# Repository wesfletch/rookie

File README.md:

# rookie

A differential-drive robot. The SBC runs ROS; an RPi Pico handles motor control and low-level I/O.

## Dev environment

Requires Docker.

```bash
# First-time setup (installs git hooks)
./rookie setup

# Build the dev container
./rookie build

# Run the dev container
./rookie run
```

All subsequent build steps run inside the container. The `src/` directory is mounted at `~/workspace/`.

## Building

See the README in each subdirectory:

- [`src/pico_interface`](src/pico_interface/README.md) — shared interface/messaging library (build first)
- [`src/rookie_pico`](src/rookie_pico/README.md) — Pico firmware
- [`src/ros`](src/ros/README.md) — ROS workspace

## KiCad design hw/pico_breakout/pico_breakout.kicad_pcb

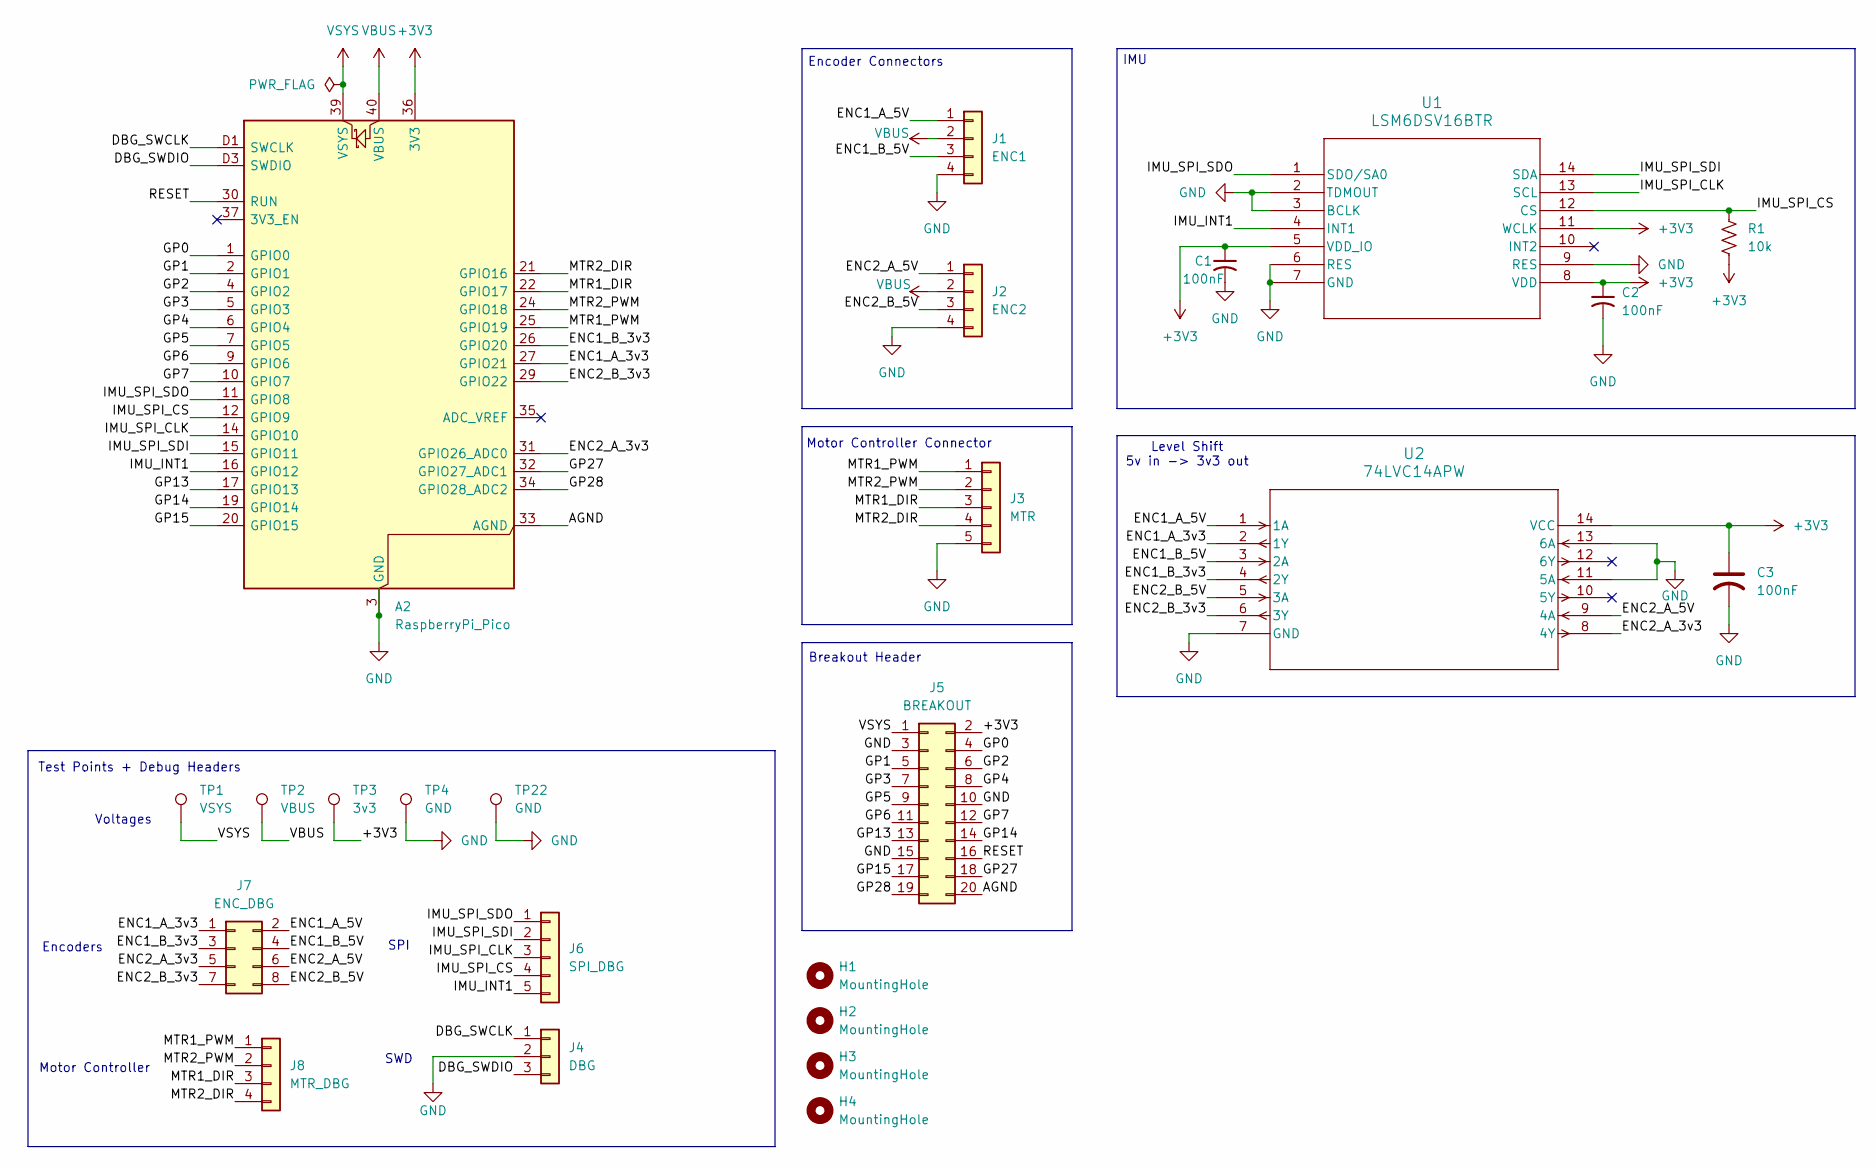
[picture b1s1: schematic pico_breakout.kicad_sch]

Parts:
A2: RaspberryPi_Pico; RaspberryPi_Pico_SMD_HandSolder
C1, C2, C3: 100nF; C_0603_1608Metric
H1, H2, H3, H4: MountingHole; MountingHole_3.2mm_M3
J1: ENC1; JST_XH_B4B-XH-AM_1x04_P2.50mm_Vertical
J2: ENC2; JST_XH_B4B-XH-AM_1x04_P2.50mm_Vertical
J3: MTR; JST_XH_B5B-XH-AM_1x05_P2.50mm_Vertical
J4: DBG; PinHeader_1x03_P2.54mm_Vertical
J5: BREAKOUT; PinHeader_2x10_P2.54mm_Vertical
J6: SPI_DBG; PinHeader_1x05_P2.54mm_Vertical
J7: ENC_DBG; PinHeader_2x04_P2.54mm_Vertical
J8: MTR_DBG; PinHeader_1x04_P2.54mm_Vertical
R1: 10k; R_0603_1608Metric
TP1: VSYS; TestPoint_Pad_D1.5mm
TP2: VBUS; TestPoint_Pad_D1.5mm
TP3: 3v3; TestPoint_Pad_D1.5mm
TP4, TP22: GND; TestPoint_Keystone_5000-5004_Miniature
U1: LSM6DSV16BTR; LGA-14L_2P5X3P0X0P83-M
U2: 74LVC14APW; SOT402-1_NEX

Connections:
+3V3: A2.36 (3V3), C1.1, C2.1, C3.1, J5.2, R1.2, TP3.1 (1_1), U1.5 (VDD_IO), U1.8 (VDD), U1.11 (WCLK), U2.14 (VCC)
/AGND: A2.33 (AGND), J5.20
/DBG_SWCLK: A2.D1 (SWCLK), J4.1
/DBG_SWDIO: A2.D3 (SWDIO), J4.3
/ENC1_A_3v3: A2.27 (GPIO21), J7.1, U2.2 (1Y)
/ENC1_A_5V: J1.1, J7.2, U2.1 (1A)
/ENC1_B_3v3: A2.26 (GPIO20), J7.3, U2.4 (2Y)
/ENC1_B_5V: J1.3, J7.4, U2.3 (2A)
/ENC2_A_3v3: A2.31 (GPIO26_ADC0), J7.5, U2.8 (4Y)
/ENC2_A_5V: J2.1, J7.6, U2.9 (4A)
/ENC2_B_3v3: A2.29 (GPIO22), J7.7, U2.6 (3Y)
/ENC2_B_5V: J2.3, J7.8, U2.5 (3A)
/GP0: A2.1 (GPIO0), J5.4
/GP1: A2.2 (GPIO1), J5.5
/GP2: A2.4 (GPIO2), J5.6
/GP3: A2.5 (GPIO3), J5.7
/GP4: A2.6 (GPIO4), J5.8
/GP5: A2.7 (GPIO5), J5.9
/GP6: A2.9 (GPIO6), J5.11
/GP7: A2.10 (GPIO7), J5.12
/GP13: A2.17 (GPIO13), J5.13
/GP14: A2.19 (GPIO14), J5.14
/GP15: A2.20 (GPIO15), J5.17
/GP27: A2.32 (GPIO27_ADC1), J5.18
/GP28: A2.34 (GPIO28_ADC2), J5.19
/IMU_INT1: A2.16 (GPIO12), J6.5, U1.4 (INT1)
/IMU_SPI_CLK: A2.14 (GPIO10), J6.3, U1.13 (SCL)
/IMU_SPI_CS: A2.12 (GPIO9), J6.4, R1.1, U1.12 (CS)
/IMU_SPI_SDI: A2.15 (GPIO11), J6.2, U1.14 (SDA)
/IMU_SPI_SDO: A2.11 (GPIO8), J6.1, U1.1 (SDO/SA0)
/MTR1_DIR: A2.22 (GPIO17), J3.3, J8.3
/MTR1_PWM: A2.25 (GPIO19), J3.1, J8.1
/MTR2_DIR: A2.21 (GPIO16), J3.4, J8.4
/MTR2_PWM: A2.24 (GPIO18), J3.2, J8.2
/RESET: A2.30 (RUN), J5.16
GND: A2.3 (GND), A2.8 (GND), A2.13 (GND), A2.18 (GND), A2.23 (GND), A2.28 (GND), A2.38 (GND), A2.D2 (GND), C1.2, C2.2, C3.2, J1.4, J2.4, J3.5, J4.2, J5.3, J5.10, J5.15, TP4.1 (1_1), TP22.1 (1_1), U1.2 (TDMOUT), U1.3 (BCLK), U1.6 (RES), U1.7 (GND), U1.9 (RES), U2.7 (GND), U2.11 (5A), U2.13 (6A)
VBUS: A2.40 (VBUS), J1.2, J2.2, TP2.1 (1_1)
VSYS: A2.39 (VSYS), J5.1, TP1.1 (1_1)

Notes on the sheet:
Encoders
Test Points + Debug Headers
Breakout Header
Encoder Connectors
Motor Controller Connector
Voltages
SWD
IMU
Motor Controller
Level Shift 5v in -> 3v3 out
SPI

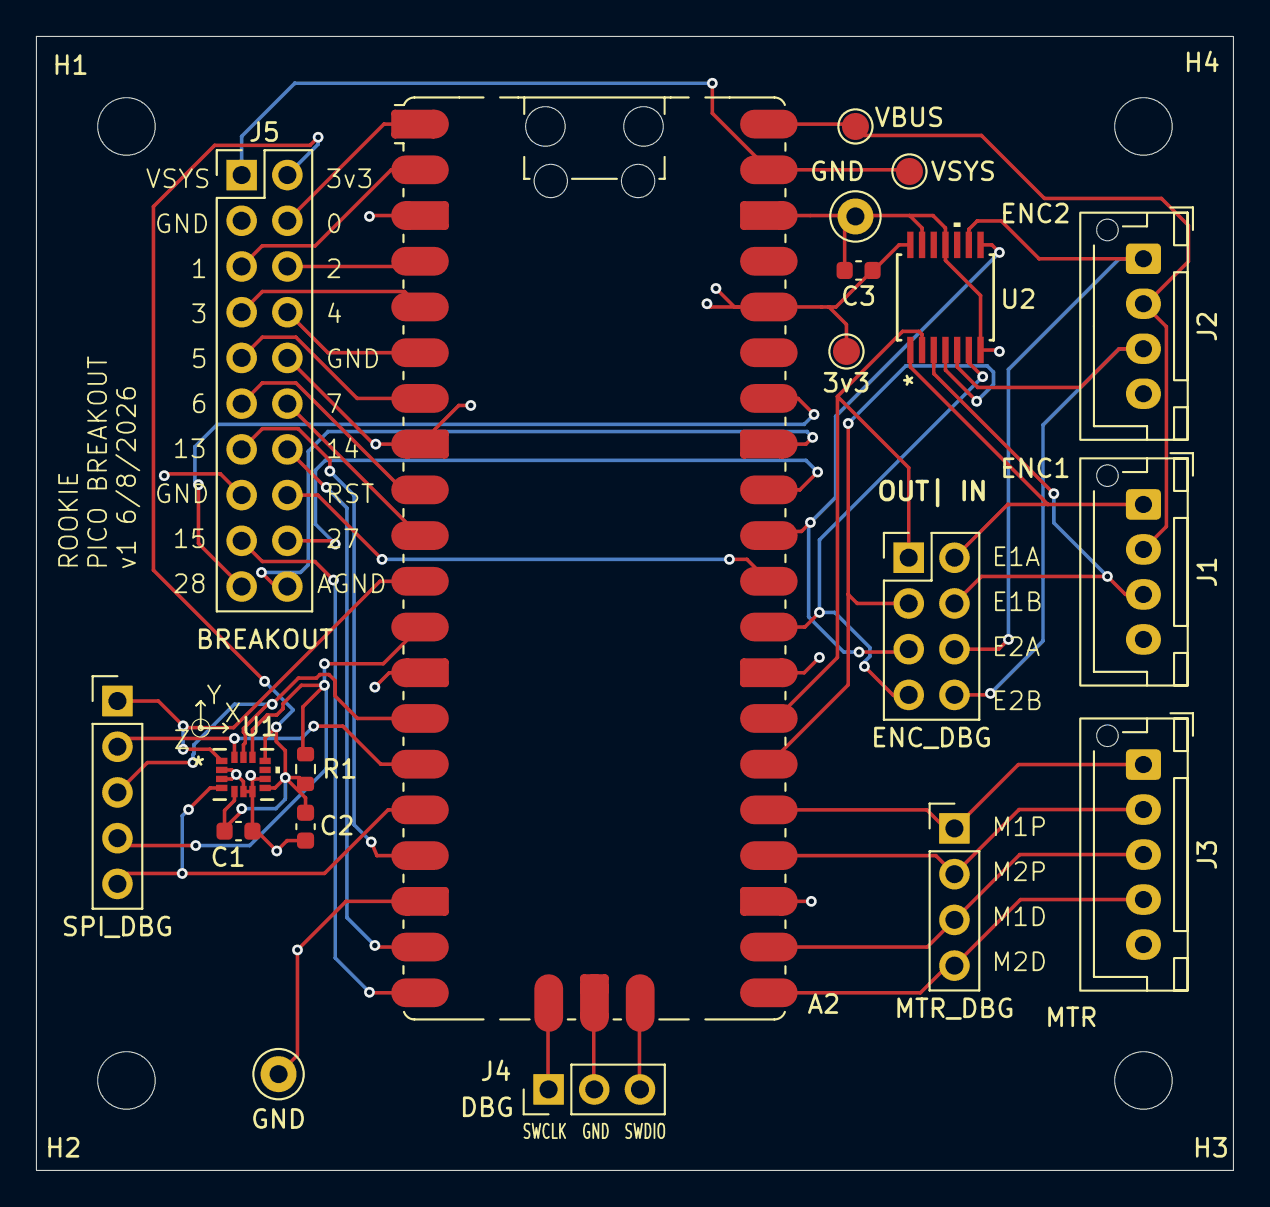
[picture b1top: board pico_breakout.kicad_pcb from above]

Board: 2 copper layers, 66.5 x 63.0 mm, 24 parts (0 on the bottom side), 38 nets.

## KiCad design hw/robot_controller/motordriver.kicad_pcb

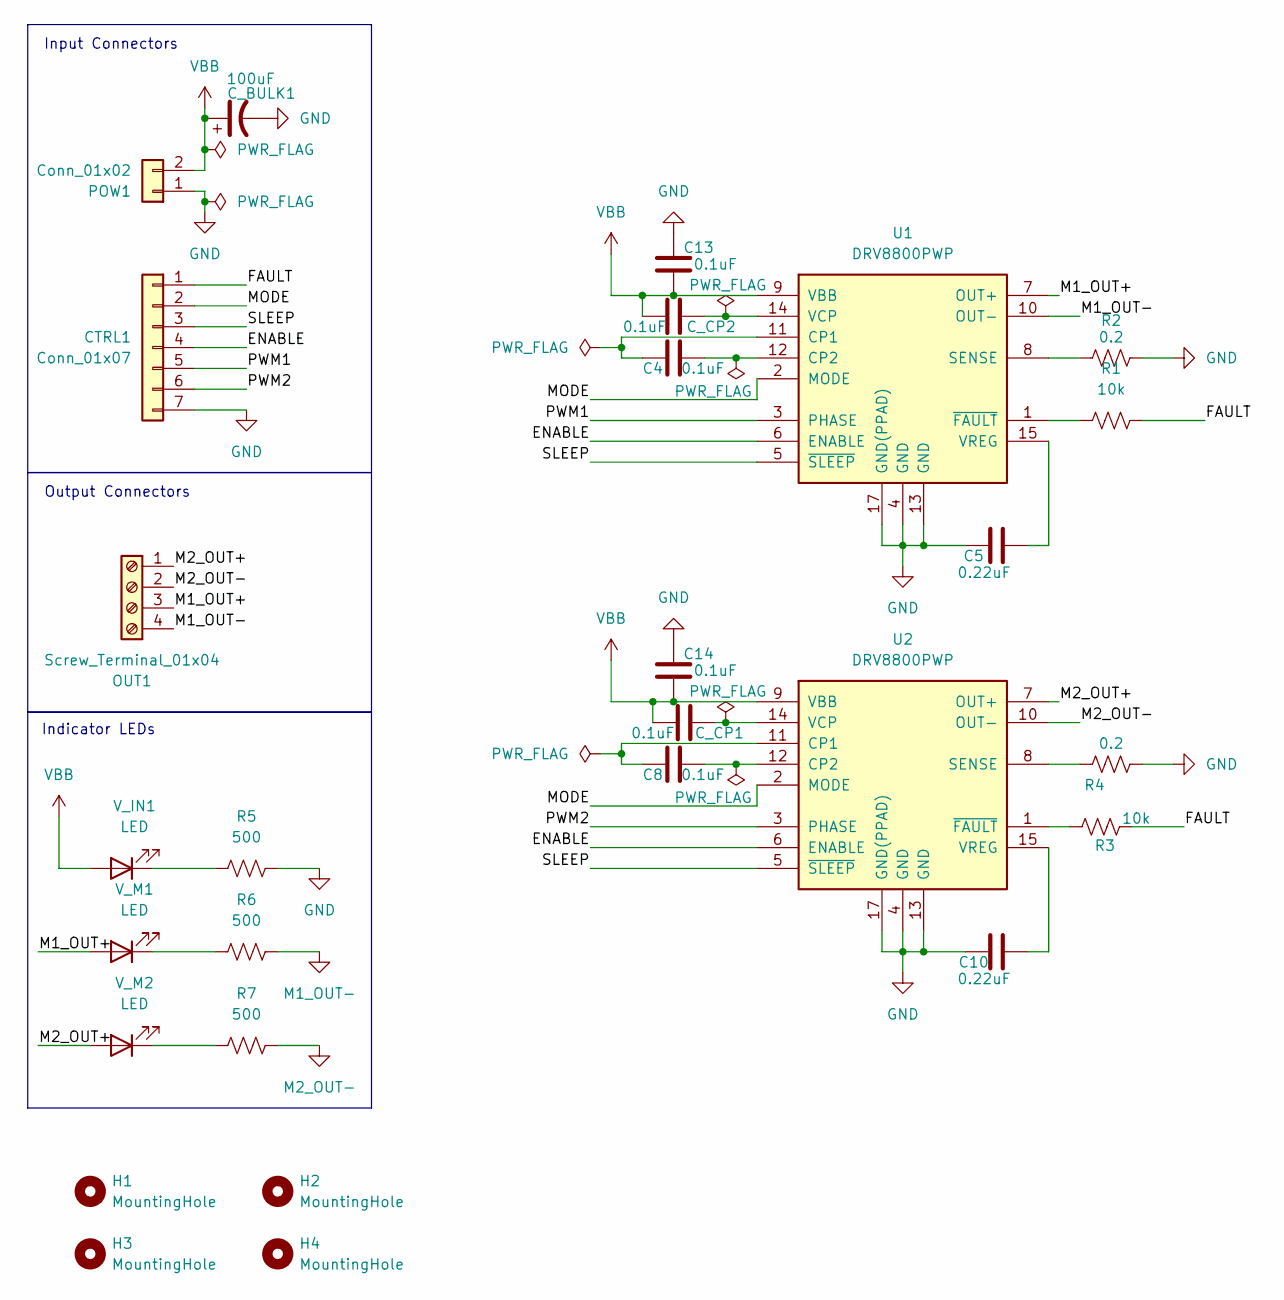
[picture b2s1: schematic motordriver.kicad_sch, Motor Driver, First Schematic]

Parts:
C4, C8, C13, C14: 0.1uF; CC0603N_YAG
C5, C10: 0.22uF; C_0603_1608Metric
CTRL1: Conn_01x07; JST_XH_B7B-XH-AM_1x07_P2.50mm_Vertical
C_BULK1: 100uF; WCAP-ASLI_6.3X5.5_DXL_
C_CP1, C_CP2: 0.1uF; CC0603N_YAG
H1, H2, H3, H4: MountingHole; MountingHole_3.2mm_M3_ISO14580
OUT1: Screw_Terminal_01x04; TerminalBlock_Phoenix_MPT-0,5-4-2.54_1x04_P2.54mm_Horizontal
POW1: Conn_01x02; AMASS_XT30UPB-F_1x02_P5.0mm_Vertical
R1, R3: 10k; R_0603_1608Metric
R2, R4: 0.2; R_0603_1608Metric
R5, R6, R7: 500; R_0603_1608Metric
U1, U2: DRV8800PWP; HTSSOP-16-1EP_4.4x5mm_P0.65mm_EP3.4x5mm_Mask3x3mm_ThermalVi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
V_IN1: LED; LED_SMLD12_ROM
V_M1, V_M2: LED; LED_SMLD12_ROM

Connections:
/ENABLE: CTRL1.4, U1.6 (ENABLE), U2.6 (ENABLE)
/FAULT: CTRL1.1, R1.1, R3.2
/M1_OUT+: OUT1.3, U1.7 (OUT+), V_M1.2 (A)
/M2_OUT+: OUT1.1, U2.7 (OUT+), V_M2.2 (A)
/MODE: CTRL1.2, U1.2 (MODE), U2.2 (MODE)
/PWM1: CTRL1.5, U1.3 (PHASE)
/PWM2: CTRL1.6, U2.3 (PHASE)
/SLEEP: CTRL1.3, U1.5 (~SLEEP), U2.5 (~SLEEP)
GND: C5.1, C10.1, C13.2, C14.2, CTRL1.7, C_BULK1.2, POW1.1, R2.2, R4.2, R5.2, U1.4 (GND), U1.13 (GND), U1.17 (GND(PPAD)), U2.4 (GND), U2.13 (GND), U2.17 (GND(PPAD))
M1_OUT-: OUT1.4, R6.2, U1.10 (OUT-)
M2_OUT-: OUT1.2, R7.2, U2.10 (OUT-)
unnamed: C4.1, U1.11 (CP1)
unnamed: C4.2, U1.12 (CP2)
unnamed: R2.1, U1.8 (SENSE)
unnamed: C_CP2.2, U1.14 (VCP)
unnamed: C5.2, U1.15 (VREG)
unnamed: R1.2, U1.1 (~FAULT)
unnamed: C8.1, U2.11 (CP1)
unnamed: C8.2, U2.12 (CP2)
unnamed: R4.1, U2.8 (SENSE)
unnamed: C_CP1.2, U2.14 (VCP)
unnamed: C10.2, U2.15 (VREG)
unnamed: R3.1, U2.1 (~FAULT)
unnamed: R5.1, V_IN1.1 (K)
unnamed: R6.1, V_M1.1 (K)
unnamed: R7.1, V_M2.1 (K)
VBB: C13.1, C14.1, C_BULK1.1, C_CP1.1, C_CP2.1, POW1.2, U1.9 (VBB), U2.9 (VBB), V_IN1.2 (A)

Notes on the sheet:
Indicator LEDs
Input Connectors
Output Connectors

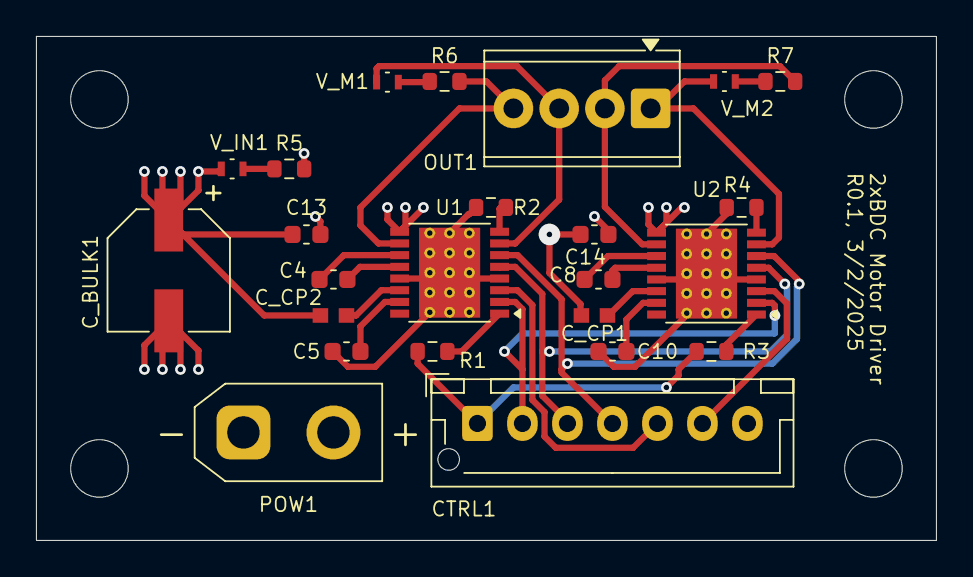
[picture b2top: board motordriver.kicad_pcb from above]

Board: 4 copper layers, 50.0 x 28.0 mm, 28 parts (1 on the bottom side), 27 nets.

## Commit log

2022-02-10 adding the pico-sdk dependency as submodule
2022-02-10 current state-of-the-art
2022-02-10 reconfigure pico-rover as standalone project
2022-02-10 add CMakeLists.txt for pico code
2022-02-10 adding seemingly useless file
2022-02-23 start pwm control for motors
2022-02-23 adds basic string in/out
2022-02-24 read incoming (from SBC) with processString()
2022-02-24 bug fix, unrecognized tokens no longer default to first else if
2022-02-25 adds ISRs for UART GPS and LORA
2022-02-27 GPS and CMD messages handled, among other things
2022-03-06 reorganizing
2022-03-07 add gitignore
2022-03-07 genericizes UART config
2022-03-08 reorg
2022-03-08 adds definitions for comm structs
2022-03-08 reorg, adds header guards
2022-03-08 documents functions
2022-03-08 rough skeleton of LoRa communication core code
2022-03-10 first attempts at LoRa multicore-ing
2022-03-10 Get LoRa working
2022-03-11 finished basic communication
2022-03-11 Add timeouts and multicore communication
2022-03-13 Add seq and ack numbers
2022-03-15 adding the gpio dep
2022-03-15 fixing circular deps by moving definitions
2022-03-15 moving UART init to main.c
2022-03-15 standalone function for UART configs
2022-03-15 motor and encoder testing
2022-03-19 Fix data parsing
2022-03-19 prep for testing
2022-03-23 latest changes for demo
2022-03-30 Add ability to reset connection after long timeout and some documentation
2022-04-06 adds function prototype to header
2022-04-06 process $MTR commands
2022-04-06 adds tachometer callback for RPM testing
2022-04-06 removes unused uart config
2022-04-06 adds persistent variables for motor commands
2022-04-06 standardize returns with EXIT_SUCCESS/FAILURE
2022-04-06 fixing status returns
2022-04-06 adds tach callback to header
2022-04-06 documentation
2022-04-06 fix status returns
2022-04-06 adds return value to initLora()
2022-04-06 fixes status returns
2022-04-06 removes unused code, adds setPWM()
2022-04-06 kill lora core if init fails
2022-04-06 replace init with status-returning version
2022-04-06 reduce console spam
2022-04-06 removes menacing space
2022-04-06 adds (commented) tachometer config
2022-04-06 clears hard-coded PWM
2022-04-06 adds sleep for timing
2022-04-06 not really sure what it thinks changed here, but
2022-04-06 fixes initLora() return value
2024-07-01 remove build artifacts
2024-07-01 gitignore
2024-08-19 fix container builds to allow for sudo
2024-08-19 start changes on serial driver
2024-08-20 dirty commit; latest working changes
2024-08-20 add submodule
2024-08-20 getting rid of local-only cruft
2024-08-20 pin submodule pico-sdk to 1.5.1 until I can figure out weird serial comms issues
2024-08-21 update dockerfile/scripting to allow building pico code directly in the dev image
2024-08-21 break pico_interface into it's own header-only interface package to be used in both pico and ROS code
2024-08-21 more gitignore stuff
2024-08-21 switch to using independent pico_interface headers
2024-08-23 heartbeat message, more dockerfile stuff, gross ROS2 shenanigans
2024-08-30 latest working version
2024-09-03 fixing the Flag, error-handling for commands, implementing ack
2024-09-03 expand gitignore, add minicom to dev images
2024-09-03 add ack to interface
2024-09-03 break serial comms onto its own core, adding fsm states
2024-09-03 nits
2024-09-05 cleaning up; finishing rough-draft of states
2024-09-05 ugly serial driver shenanigans; beginnings of 'deploy' workflow; very very very TODO
2024-09-09 dirty
2024-09-12 refactor/cleanup
2024-10-26 cleaning up pico_interface and the rookie container
2024-10-26 cleanup, attempting to diagnose command prefix matching bug
2024-10-26 move encoder reading from "callback" to "task" format
2024-10-26 attempt to stop getting spammed by pico-sdk build artifacts
2025-03-06 working encoders
2025-03-06 dirty commit, still trying to figure out weird callback matching bug
2025-03-06 add static checker 'cppcheck' to dev image
2025-03-07 bikeshedding: generate python classes for pico_interface based off of yaml file
2025-03-07 still cannot reproduce matching bug...
2025-03-21 more dev dependencies
2025-03-28 fix pipx package name
2025-03-28 slightly less bad bash script
2025-03-28 refactoring mobility_driver to actually work, plus or minus some weird device name issues
2025-03-28 kill worthless line
2025-03-31 more creature comforts for the dev container
2025-03-31 update MobilityDriver to use threads + queue for inputs and outputs
2025-03-31 first draft estop service; I might want a normal pub-sub topic instead...
2025-03-31 always name the dev container SOMETHING so that I can re-attach later
2025-03-31 cleanup
2025-03-31 break MessageData methods out of MobilityDriver
2025-04-01 MobilityDriver: added callback mechanism for received messages
2025-04-03 WIP robot description for rookie
2025-04-03 cleanup, more docker dependencies
2025-04-04 working tree
2025-04-07 fixing docker images
2025-04-09 add bashrc so my terminal isn't ugly
2025-04-09 attempting to get gazebo sim working
2025-04-09 allow force-rebuild of dev container with --no-cache
2025-04-10 rookie in sim, commandable, can receive sensor data; BIG TODO: fix the TF frames for the wheels
2025-04-11 add gitignore for urdf
2025-04-11 fixed tf tree for wheels, robot is drivable
2025-04-11 get rid of autogenerated file
2025-04-11 fix gitignore
2025-04-14 more simulation setup
2025-04-15 checkpoint: working odom->base_link transform and EKF-ed odometry in simulation
2025-04-15 pretty output
2025-04-15 being forced off of ROS rolling by navigation2; back-porting to ROS jazzy
2025-05-06 add deps to dev container
2025-05-06 dirty: cleanup, attempt to add odom to base driver
2025-05-06 dirty: config for nav, gazebo, rviz, and colcon ws
2025-05-06 dirty: cmake changes for clangd and odom output
2025-06-17 support for empty pico_interface messages, e.g., the new RESET command
2025-06-17 convenience function for building the pico firmware in the dev environment
2025-06-17 cleanup + documentation
2025-06-17 initial commit for the 'console' dev-tool for pico_interface
2025-06-17 add half-hearted support for the "RESET" command from pico_interface
2025-08-27 Switch pico-sdk dep from a submodule to a FetchContent call
2025-08-27 move pico_interface scripts into their own dir
2025-08-27 Cleanup the rookie executable
2025-08-27 Give up on custom serialization format; switching to just use protobufs
2025-08-27 Don't know why I wrote this, but I'll check it in I guess
2025-08-27 Add fetchcontent dir to gitignore
2025-09-05 update project to keep all code (including ros code) under src/; cleanup and compiler nonsense
2026-04-02 I don't really remember everything I did here, but I vaguely recall something about getting fed up with using nanopb through cmake and just scripting it; then something about starting work on an outb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
2026-04-18 believe it or not, more build fixes; a bunch of "best practices" nanny stuff
2026-04-18 testing the hooks
2026-04-18 Revert "testing the hooks"
    This reverts commit fd28f3030da938348e83d88784485b86dede5a7f.
2026-04-18 expanding pre-commit hooks
2026-04-21 Switch protos to using the nanopb msg ID functionality to automatically assign IDs
2026-04-21 pre-commit nonsense
2026-04-21 more clang-format stuff
2026-04-21 auto-formatting with clang-format (hideous, but I'll get over it)
2026-04-21 radical monorepoism: even the electrical designs
2026-04-24 I'm allowed to have my .vscode folder here, what are you gonna do about it?
2026-04-24 more build setup nonsense
2026-05-08 slopbot assisted rewrite of console.py, needs an actual human to go back and clean it up now...
2026-05-08 fully convert pico_interface to use protobuf messaging instead of custom text serialization; cpp and python package generation
2026-05-08 upgrade pico-sdk version from 1.5.x to 2.2.x
2026-05-08 dev env and build instructions, since I keep forgetting
2026-05-08 big update: move to the new pico_interface proto messaging; general cleanup from SD-era code; outbound messaging moved to queue instead of direct sends, inbound/outbound messaging now handled by core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
    next steps are tightening up control loops and actually hooking this thing back up to the (now-dusty) robot
2026-06-07 localize pin config to a single file
2026-06-13 rookie pico_breakout v1 finalized, updates to Pins.hpp file in firmware to match
2026-06-13 add clang-tidy precommit checks
2026-06-13 encoder test cleanup; really just testing the pre-commit hook
2026-06-18 install `uv` in dev container by default
2026-06-18 move the `encoder_test` executable to using the central Pins.hpp file
2026-06-18 Adds basic firmware support for LSM6DSV IMU; currently blocking/polling reads over SPI
2026-06-18 new hw symbols and footprints
2026-06-18 add clock abstraction to help with (eventual) mocking; plus we get a messagehandler for free
2026-06-18 adjust accelerometer FS for more granularity, at the cost of a narrower range
2026-06-18 Add support for coordinate transforms to the IMU via a generic, compile-time validated Frame construct; wire the IMU to report via the Imu.proto message; general cleanup
2026-06-18 fix the dumb python import bug in protoc, just like every other time I've ever used it
2026-06-18 udpate console to pull in pico_interface as editable, to get around annoying caching. Also, the linter decided to change stuff in here. Who cares.
